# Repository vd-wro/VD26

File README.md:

# WRO VizDrive 2026

Welcome to the project repository for the **Panamanian 🔴⚪🔵 Team VizDrive** for the **World Robot Olympiad (WRO)** 2026!
Here you will find all the documentation, source code, images, and models related to our autonomous robot.

## About VizDrive's Legacy

VizDrive started in 2025, and now keeps thriving with the same young Panamanians that started the project. For this updated 2026 repository, we have kept ViZio's previous versions for better understanding and comparison from our engineering process.

## Project Summary

VizDrive's core, ViZio, is an autonomous robot designed to navigate a closed-loop circuit, maintaining a stable trajectory with gyroscopic correction. It uses artificial vision, in conjunction with ultrasonic and color sensors, to detect walls and avoid obstacles.

We are participating in the **Future Engineers Category** to develop our skills and demonstrate the capabilities of young Panamanians in a competitive field like robotics.

During the creation of our robot, we tried to push the **fundamentals of robotics** to the highest we could. As you go through this GitHub repository, you may notice that we worked with very basic sensors (the kind typically found in standard Arduino kits), and that we strived to optimize them to the best of our capacities. This is because we aimed to make our build accessible for everyone, and show that even with the simplest components, it is possible to create truly functional robotic systems.

We would like to invite you into this short, 3 minute summary video to have a fresh start on our robot's construction, logic, and GitHub organization.

> [!NOTE]
> Throughout the competition, we are constantly making modifications in the software and hardware of our robot. We try to update on all the changes we make, but if you notice any inconsistency between the pages of the documentation, please let us know!

---

## General Project Index

You can use this index to navigate through our robot's documentation. Each document provides detailed information on every aspect of its operation:

* [**1. General Project Overview**](./docs/01_project_overview.md)
  * General and concise introduction to the robot and its main components.
  * Describes the robot's operational phases and workflow diagram.
* [**2. Hardware and Components of the Robot**](./docs/02_hardware_components.md)
  * Detailed specifications of all integrated electronic and mechanical hardware.
  * [General Electromechanical Diagram](./schemes/electromechanical_diagram.png)
  * [Circuit Interactive Design (Cirkit)](https://vd-wro.github.io/VD26/embeds/interactive_circuit)
  * [KiCad Files](./src/kicad_pcb)
* [**3. Software Architecture**](./docs/03_software_architecture.md)
  * Overview of software libraries, core functionalities, and code structure.
  * [Autonomous Driving Code](./src/main_control/Vizdrive_WRO_code.ino)
* [**4. Sensor and Pin Configurations**](./docs/04_sensors_and_pin_configuration.md)
  * In-depth review of each sensor, its role in the functionality, and Arduino pin assignments.
  * [Sensors' Test Codes](./src/test_code/)
* [**5. Robot Mobility Functionality**](./docs/05_robot_mobility.md)
  * Focuses on the robot's motion system, motor configuration, and steering mechanisms.
* [**6. PID Control for the Gyroscope**](./docs/06_pid_gyroscope_control.md)
  * Explains the MPU gyroscope implementation and PID control for trajectory stability.
  * [MPU Calibration Code](./src/mpu_orientation_control/mpu_calibration/mpu_calibration.ino)
  * [MPU Calibration Data Graph](./assets/data_graphs/MPU%20Calibration%20Data%20Analysis.xlsx)
* [**7. Computer Vision Functions**](./docs/07_computer_vision.md)
  * Covers the PixyCam's vision-based obstacle evasion.
  * [Computer Vision Code](./src/computer_vision/computer_vision.ino)
* [**8. Ultrasonic Distance Sensing and PID**](./docs/08_ultrasonic_distance_sensing.md)
  * Covers the distance measurement and wall avoidance with ultrasonic sensors, and the filters implemented to adjust precision.
  * Introduces and explains the side PID system for straight-line driving.
  * [Ultrasonic Sensor Data Analysis](./assets/data_graphs/Ultrasonic%20Sensors%20Data%20Analysis.xlsx)
* [**9. Color Detection Functions**](./docs/09_color_detection.md)
  * Explains the color sensor's applications and calibration.
* [**10. 3D Modeling and Fabrication**](./docs/10_3d_modeling.md)
  * Details the 3D design process, mechanical characteristics, and fabrication parameters.
  * [3D Models STL](./models/)
* [**11. Other Resources and User Manual**](./docs/11_other_resources.md)
  * User manual for robot's operation and calibration.
  * Summarized documentation and additional relevant resources and materials.
  * Highlighted technical issues and applied fixes.
* [**12. Building Instructions**](./docs/12_building_instruction.md)
  * Visual resources and explanations for ViZio's construction.
  * Construction animations and renders.

---

## ViZio Versions

| Versions                  | Problems | Improvements made          | Used In          | 
| :--------------------------- | :--------------------------- | :------------------------------------------- | :--------------------------------- | 
| Prototype               |     Often finding disconnected components.                    | N/a               | First prototype made. |
| ViZio                |     Gyroscope calibration, partial parking, connection problems due to cable wear, complications with the dual ultrasonic sensor. radar.                    | Removed clutter with a hand-soldered PCB.                 | 🇵🇦 Regionals 2025 |
| ViZio 2.0     |          Challenges with Pixy Parameters' calibration, incomplete parking maneuver, inverted SDA and SCL pins.          | Improved PCB, kept one frontal ultrasonic, new logic for parallel parking.      | 🇵🇦 National 2025 |
| ViZio V3                   |          Block color detection through Pixy, slower velocity.                | Fixed PCB, adaption to camera bug, new parallel parking logic that includes last block evasion.                 | 🇸🇬 WRO 2025 |
| ViZio IV    |      Poor power distribution caused servo peaks to drain the battery     | Changed camera, improved chassis, upgraded PCB, and added mechanical differential.      | 🇵🇦 Regionals & National 2026 |
| ViZio Phase V    |  N/a  | Coming soon...      | 🇵🇷 WRO 2026 |

For better comprehension please visit [**Previous Versions of our Robot**](./docs/11_other_resources.md#119-version-history)

---

## Photos and Videos

* **Team Photos:** [View Photos](./t-photos/README.md)
* **Vehicle Photos:** [View Photos](./v-photos/README.md)
* **Demonstration Videos:** [View Videos](./video/README.md)

---

## Source Code

All control and test codes are located in the `src/` folder.

* [Autonomous Driving (Obstacle Avoidance)](./src/main_control/Vizdrive_WRO_code.ino)
* [Autonomous Driving (No Obstacle Avoidance)](./src/main_control/Open_Round.ino)
* [MPU Orientation Control (PID and Calibration)](./src/mpu_orientation_control/pid_gyroscope.ino)
* [Computer Vision (PixyCam 2.1)](./src/computer_vision/computer_vision.ino)
* [Sensors' Test Codes](./src/test_code/)

---

## 3D Models

Files for 3D printed components are located in the `models/` folder in `.stl` files.
To access interactive models of each component, hosted in GitHub pages, visit `embeds/`.

* [Robot 3D Models](./models/)
* [Interactive 3D Models](./embeds/)

A version of our Unity Simulator, used during the robot's construction and planification process, is available as an HTTP embed, hosted with GitHub pages.

* [Unity Simulator Information](./embeds/Unity_simulator)
* [Unity Web Player](https://vd-wro.github.io/VD26/embeds/Unity_simulator/)

---

## Diagrams and Graphs

Flowcharts, circuits, and relevant data graphs.

* [Operation Flowcharts](./assets/flowcharts)
* [Calibration Data Graphs](./assets/data_graphs/)
* [Additional Hardware Photos](./assets/hardware_photos/)

---

## Team Members 🙋‍♂️🙋‍♀️🙋

|                                                       |                                                              |                                                        |
|:-----------------------------------------------------:|:-----------------------------------------------------------:|:-------------------------------------------------------:|
|        |  |              |
| [**ALEXIS PALACIOS NG**](./t-photos/meet_the_team/Alexis.md) <br> *Software Engineer*       | [**AISLINN CHAWLA ARORA**](./t-photos/meet_the_team/Aislinn.md) <br> *Logistics and Creativity*        |  [**CARLO HO NG**](./t-photos/meet_the_team/Carlo.md) <br> *Hardware Engineer*   |
Sensor Integration, <br>Firmware Architecture, <br>Code Logic, <br>Error Management, <br>Data Analysis, <br>GitHub Repository | Engineering Journal, <br>Drafting, <br>GitHub Repository, <br>Soldering, <br>Photography and Film, <br>Competition Planning|  Construction, <br>Wiring, <br>Circuit and PCB Design, <br>Power Management, <br>3D Modeling and Planning, <br>Animation, Illustration, Editing  |

---

## Special Thanks

We are profoundly thankful to everyone who has supported us on our journey so far! We're incredibly grateful to our school administration for providing the resources and trust needed to pursue this challenge. To our teachers, thank you for your guidance and advice during our preparation; we especially appreciate your patience with our absences for robot practices (we promise to catch up on our assignments after the Olympiad 😅). A special shout-out to our friends who spent their free time supporting us, cheering us on, and helping us stay up to date. To our amazing parents, your assurance and belief in us have been the foundation of our efforts, allowing us to participate even though it meant missing many classes. And last but certainly not least, to our incredible coach, Professor Agustín Rogelio Orro Pérez. Even while mentoring five other teams, you still found time to guide us through it all. Your expertise, leadership, and dedication have been invaluable for us.

Thank you all!

---

For any inquiry, question, or recommendation, feel free to contact us via email: **<vizdrive.wro@gmail.com>**

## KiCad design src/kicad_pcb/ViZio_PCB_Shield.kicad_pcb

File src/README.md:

# Souce Code Directory

Here you can find all the .ino files for the operation of our robot in the Open and Obstacle Challenges.
As well, you can find the test codes we used throughout the process of construction and debugging, besides the codes for data recolection and analysis for the ultrasonic sensors and the MPU6050.

The directory is organized in the following way:

## `src/07_computer_vision`

You will find the test code for the Pixycam 2.1 artificial vision and color signature detection. 

## `src/main_control`

You'll find the updated main code for the WRO competition challenges.

When you refer to the main source code, please consider that it is updated throughout the competition to improve or add different features, so it may vary between rounds.
In particular, the PID control constants, the amount of correction, and the different thresholds are modified depending on the performance.
You can see progress and changes over time by viewing previous versions in GitHub commits.

## `src/mpu_orientation_control`

You will find the test code and data recolection code for the MPU6050 gyroscope + accelerometer.

## `src/ultrasonic_sensors`

You will find the test code for raw measurements, the test code for filtered measurements, and the code for data recolection to compare how the error dispersion varies between raw and filtered measurements.

## `src/test_code`

You will find the general test codes for other functionalities as the color sensors suite, mainly to adjust the thresholds, or a code to test the motor and IR encoder.

## `src/kicad_pcb`

You will find the circuit files for our custom PCB.

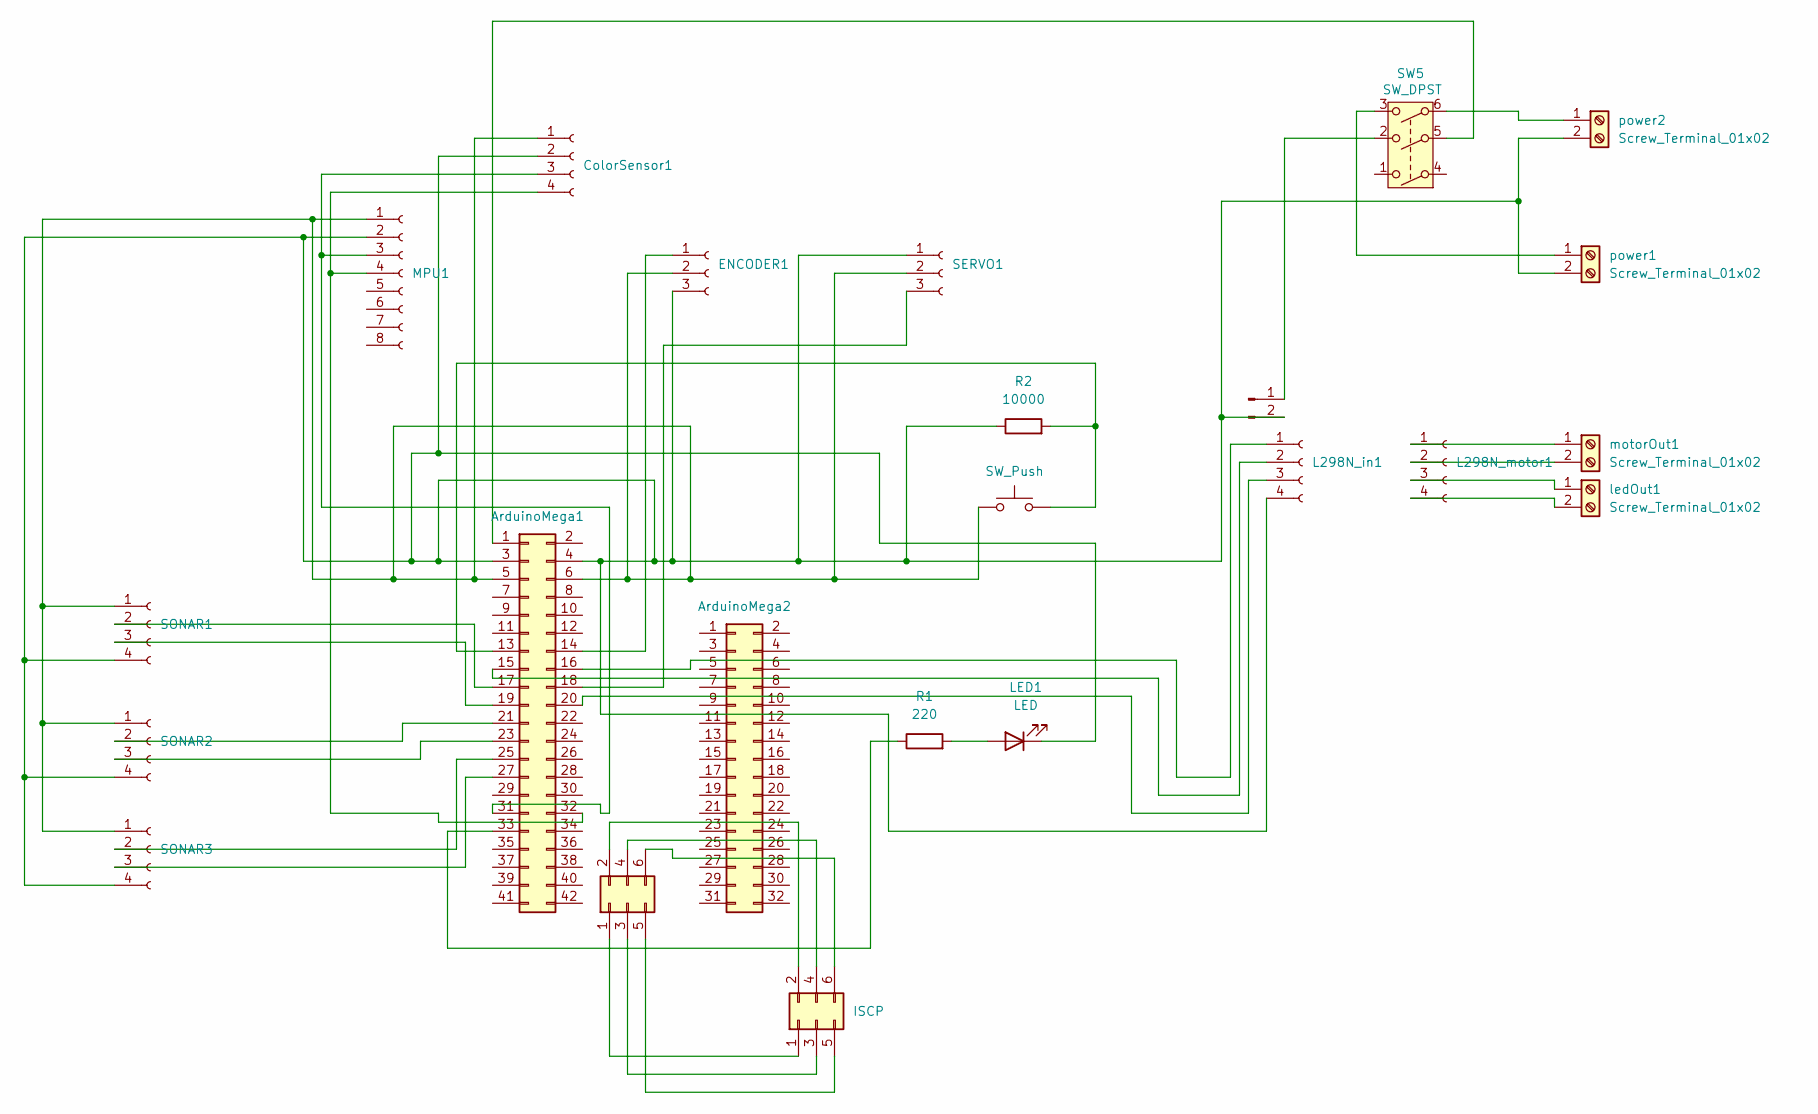
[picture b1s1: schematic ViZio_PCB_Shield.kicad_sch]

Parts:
ColorSensor1: Conn_01x04_Socket; PinSocket_1x04_P2.54mm_Vertical
ENCODER1: Conn_01x03_Socket; PinSocket_1x03_P2.54mm_Vertical
J1: ArduinoMega1; PinSocket_2x21_P2.54mm_Vertical
J2: ISCP; PinHeader_2x03_P2.54mm_Vertical
J3: ArduinoMega2; PinSocket_2x16_P2.54mm_Vertical
J4: Conn_02x03_Odd_Even; PinSocket_2x03_P2.54mm_Vertical
L298N_in1, L298N_motor1: Conn_01x04_Socket; PinSocket_1x04_P2.54mm_Vertical
L298N_power1: Conn_01x02_Pin; PinSocket_1x02_P2.54mm_Vertical
LED1: LED; LED_D5.0mm
MPU1: Conn_01x08_Socket; PinSocket_1x08_P2.54mm_Vertical
R1: 220; R_Axial_DIN0207_L6.3mm_D2.5mm_P10.16mm_Horizontal
R2: 10000; R_Axial_DIN0207_L6.3mm_D2.5mm_P10.16mm_Horizontal
SERVO1: Conn_01x03_Socket; PinHeader_1x03_P2.54mm_Vertical
SONAR1, SONAR2, SONAR3: Conn_01x04_Socket; PinSocket_1x04_P2.54mm_Vertical
SW1: SW_Push; SW_PUSH_6mm_H5mm
SW5: SW_DPST; SW_Push_2P2T_Toggle_CK_PVA2OAH5xxxxxxV2
ledOut1: Screw_Terminal_01x02; TerminalBlock_bornier-2_P5.08mm
motorOut1: Screw_Terminal_01x02; TerminalBlock_bornier-2_P5.08mm
power1, power2: Screw_Terminal_01x02; TerminalBlock_bornier-2_P5.08mm

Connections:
unnamed: ColorSensor1.2 (GND), ENCODER1.3 (GND), J1.3 (GND), J1.4 (GND), L298N_in1.4 (IN4), L298N_power1.2 (-), LED1.1 (K), MPU1.2 (GND), R2.1, SERVO1.1 (GND), SONAR1.4 (GND), SONAR2.4 (GND), SONAR3.4 (GND), power1.2 (-), power2.2 (-)
unnamed: ColorSensor1.3 (SCL), J1.31 (D21), MPU1.3 (SCL)
unnamed: ColorSensor1.4 (SDA), J1.32 (D20), MPU1.4 (SDA)
unnamed: ColorSensor1.1 (VCC), ENCODER1.2 (VCC), J1.5 (5V), J1.6 (5V), MPU1.1 (VCC), SERVO1.2 (VCC), SONAR1.1 (VCC), SONAR2.1 (VCC), SONAR3.1 (VCC), SW1.1
unnamed: ENCODER1.1 (OUT), J1.14 (D2)
unnamed: J1.13 (D3), R2.2, SW1.2
unnamed: J1.16 (D4), L298N_in1.1 (IN1)
unnamed: J1.15 (D5), L298N_in1.2 (IN2)
unnamed: J1.18 (D6), SERVO1.3
unnamed: J1.17 (D7), SONAR1.2 (TRIG)
unnamed: J1.20 (D8), L298N_in1.3 (IN3)
unnamed: J1.19 (D9), SONAR1.3 (ECHO)
unnamed: J1.21 (D11), SONAR2.2 (TRIG)
unnamed: J1.23 (D13), SONAR2.3 (ECHO)
unnamed: J1.25 (D15), SONAR3.2 (TRIG)
unnamed: J1.27 (D17), SONAR3.3 (ECHO)
unnamed: J1.33 (D23), R1.1
unnamed: J1.1 (VIN), SW5.5
unnamed: J2.1, J4.1
unnamed: J2.2, J4.2
unnamed: J2.3, J4.3
unnamed: J2.4, J4.4
unnamed: J2.5, J4.5
unnamed: J2.6, J4.6
unnamed: L298N_motor1.2 (MOTOR_A2), motorOut1.2 (-)
unnamed: L298N_motor1.1 (MOTOR_A), motorOut1.1 (+)
unnamed: L298N_motor1.4 (MOTOR_B2), ledOut1.2 (-)
unnamed: L298N_motor1.3 (MOTOR_B), ledOut1.1 (+)
unnamed: L298N_power1.1 (+), SW5.2
unnamed: LED1.2 (A), R1.2
unnamed: SW5.3, power1.1 (+)
unnamed: SW5.6, power2.1 (+)

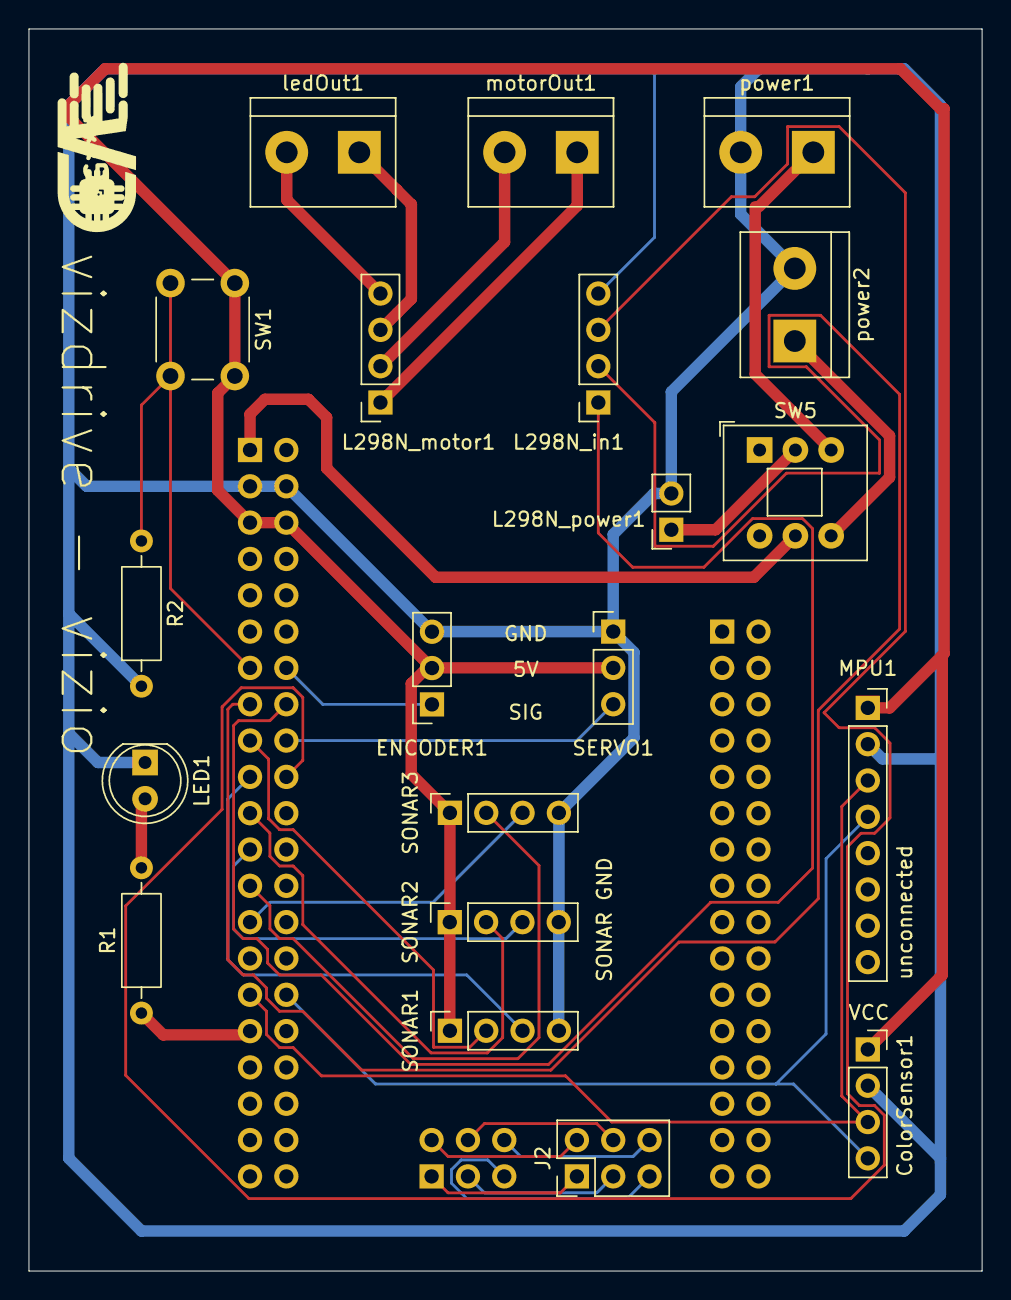
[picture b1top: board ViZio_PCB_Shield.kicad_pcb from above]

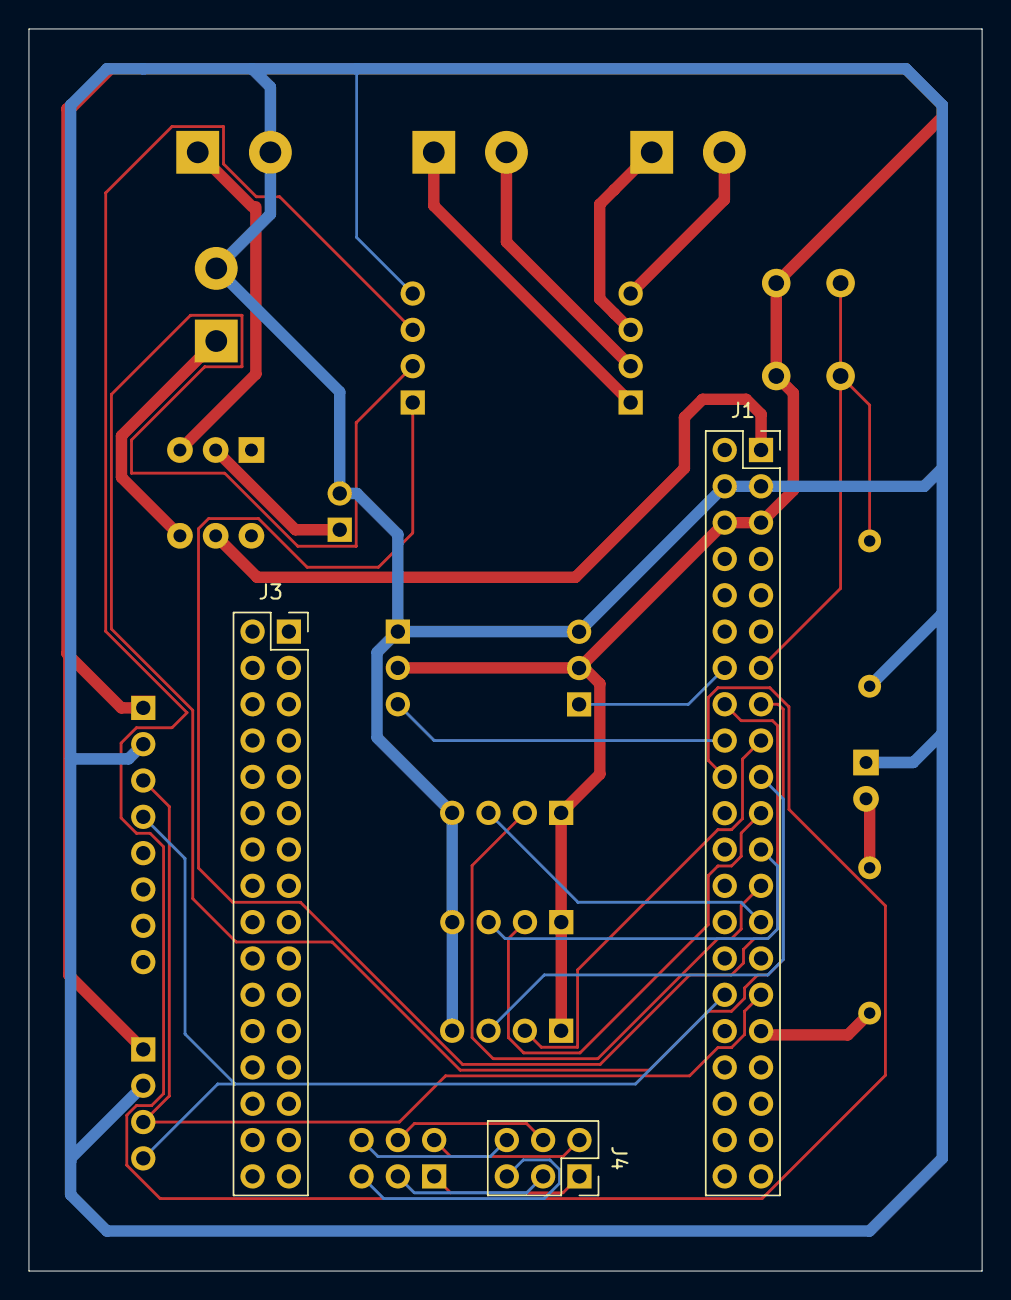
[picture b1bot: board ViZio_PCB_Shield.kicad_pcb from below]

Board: 2 copper layers, 66.7 x 86.9 mm, 23 parts (3 on the bottom side), 32 nets.

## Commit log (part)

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2025-07-08 Replaced the motor driver image
2025-07-08 Update 09_color_detection.md
    Added the precise color detection calculation
2025-07-08 Update 01_project_overview.md
    Clarification of the functionalities of the Open Challenge and the Obstacle Challenge.
2025-07-08 Update 03_software_architecture.md
    Explanations on the Open Round vs Challenge Round functionalities.
    Clarifications on the safeDelay() function.
2025-07-08 Update 04_sensors_and_pin_configuration.md
    Edited the ultrasonic configuration.
2025-07-08 Update 05_robot_mobility.md
    Added the exitParking() function
2025-07-08 Update 06_pid_gyroscope_control.md
    Modifications and clarifications on the calibration code.
2025-07-08 Update 07_pixycam_computer_vision.md
    Updated the new mechanism, PixyCam configuration and parameters and others.
2025-07-08 Update 08_ultrasonic_distance_sensing.md
    Updated the constrasting functions of the Open Challenge Round and the Obstacle Challenge Round.
2025-07-08 Update 09_color_detection.md
    Added the handleColorAction() function according to the Challenge.
2025-07-08 Update 06_pid_gyroscope_control.md
    Added hyperlink to 09_color_detection.md
2025-07-08 Update 11_other_resources.md
    Added the ultrasonic data graph. More to add into the miscelaneous section.
2025-07-09 Update README.md for embeds
2025-07-09 Update README.md for Unity Simulator
2025-07-09 Uploaded a web capture
2025-07-09 Update README.md
    For aesthetics
2025-07-09 Create README.md for hardware_photos
    Parcial creation of the hardware photos information.
2025-07-09 Update 09_color_detection.md
    Corrections.
2025-07-09 Uploaded the .gif of the logo
2025-07-09 Rename aislinn_1.jpg to aislinn_3.jpg
2025-07-09 Added the team member's photos
2025-07-09 Created README.md for the t-photos folder
2025-07-10 Update README.md for the video folder
2025-07-10 Upload the vehicle photos from all angles
2025-07-10 Create README.md for v-photos
2025-07-10 Update README.md
    Update links to photos and code
2025-07-10 Update README.md for videos
    Added the construction and music videos
2025-07-10 Uploaded the ultrasonic median filter code
2025-07-10 Update 11_other_resources.md
    Added the user manual.
2025-07-10 Update README.md for hardware photos
2025-07-10 Update README.md
    grammar
2025-07-10 Update Vizdrive_WRO_code.ino
    Updated the newest version of our code.
2025-07-12 Create Carlo.md for Meet The Team
2025-07-12 Create Aislinn.md for Meet The Team
2025-07-15 Update 02_hardware_components.md
    Updated the energy source
2025-07-15 Uploaded the 4.2V battery img
2025-07-29 Update 02_hardware_components.md
    Error 404
2025-07-29 Update README.md
    error 404
2025-09-30 Updating Github
2025-09-30 Added the kicad scheme
2025-10-01 Bug Fixes
2025-11-16 Added V3 Logo
2025-11-18 Updating src/kicad_pcb directory
2025-11-18 Create kicad_pcb
2025-11-18 Create file
2025-11-18 Revise hardware components documentation
2025-11-18 Document I2C bus fix and update images
2025-11-18 Update I2C bus images in hardware components documentation
2025-11-18 Fix image height in hardware components documentation
2025-11-19 Update 3D model links in documentation
    Added final and international 3D model links for the chassis.
2025-11-19 Fix grammar and clarity in ViZio 2.0 section
    Corrected grammatical errors and improved clarity in the description of ViZio 2.0.
2025-11-19 Fix typos in ViZio documentation
    Corrected typos and improved clarity in the documentation for the ViZio robot versions.
2025-11-19 Add link to International 3D Model for chassis
    Added link to the International 3D Model of the chassis.
2025-11-19 Fix link to 3D Modeling document
    Updated the reference link to the 3D Modeling document for better clarity.
2025-11-19 Update README with new chassis information
2025-11-19 Fix formatting in README.md for chassis section
2025-11-19 Update README with International Robot details
2025-11-19 Fix file name for International Chassis in README
    Corrected the file name for the International Chassis in the table.
2025-11-19 Update README with new chassis model information
2025-11-19 Correct formatting for Pivoting Maneuvers section
    Fixed formatting issue in the documentation regarding pivoting maneuvers.
2025-11-19 Change ViZio V3 image from PNG to JPG
    Updated image format for ViZio V3 hardware photo.
2025-11-19 Change ViZio 2.0 image in other resources
    Updated image reference for ViZio 2.0 in documentation.
2025-11-19 Document realignment method for robot positioning
    Added a realignment method for the robot to bump against the outer wall for better positioning.
2025-11-19 Fix formatting and punctuation in technical issues section
    Corrected formatting and punctuation in the technical issues section for clarity.
2025-11-19 Updated avoidWallPID function details
    Updated the section on the avoidWallPID function to clarify its purpose, operation, and the conditions under which it runs. Added detailed explanations for timing control, error calculation, and yaw 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
2025-11-19 Refine documentation for ultrasonic distance sensing
    Updated explanations for sonar sensor setup and PD control logic.
2025-11-19 Refactor avoidWallPID section for clarity
    Updated the formatting and structure of the section on the avoidWallPID function to improve clarity and readability.
2025-11-19 Fix formatting and update ultrasonic distance sensing doc
2025-11-19 Enhance documentation for avoidWallPID function
    Expanded the explanation of the avoidWallPID function, detailing its purpose, operation, timing control, setup, lateral PD control, yaw adjustment logic, and new target yaw application.
2025-11-19 Add avoidWallPID function code snippet
    Added code snippet for avoidWallPID function.
2025-11-19 Fix formatting of avoidWallPID code
    Updated code block formatting for avoidWallPID function.
2025-11-19 ViZio V3 New Images
2025-11-19 Updated robot pictures.
    Changed all the pictures to the new ViZio V3 International bot pictures.
2025-11-19 Enhance documentation with delay functions table
    Added a table summarizing delay functions and their purposes.
2025-11-19 Update section numbers in software architecture doc
2025-11-19 Update documentation for safeDelay functions
    Clarify the purpose and operation of safeDelay functions in the documentation.
2025-11-19 Fix duplicate line in software architecture documentation
2025-11-19 Replace safeDelay with safeDelayColor in evasion logic
    Updated delay functions to use safeDelayColor for better handling of yaw error during evasion.
2025-11-19 Update contact information section in documentation
    Removed and then re-added contact information for feedback and inquiries.
2025-11-19 Document performance improvement by soldering MPU
    Added a note on the performance improvement achieved by soldering the MPU to reduce vibrations.
2025-11-19 Update Pixy calibration instructions for clarity
    Clarified instructions for Pixy calibration regarding lens covering during initialization.
2025-11-19 Update team member skills in README
2025-11-19 Updated description of ViZio's name
2025-11-19 Revise video links and add new video explanation
    Updated video links and descriptions in README.
2025-11-19 Clarify robot animation video content in README
    Updated the README to clarify the purpose of the robot animation videos and added a link to the first video.
2025-11-20 Rename embeds/ViZio_PCB.glb to embeds/models_glb/ViZio_PCB.glb
2025-11-20 Create Interactive_KiCad_PCB
2025-11-20 Rename Interactive_KiCad_PCB to Interactive_KiCad_PCB.html
2025-11-21 Update 01_project_overview.md
    Updated the Flow Diagram
2025-11-21 Rename flowchart.png to previous_flowchart.png
2025-11-21 Upload the new workflow diagrams
2025-11-21 Create README.md for Workflow Diagrams
2026-06-16 Update project year from 2025 to 2026
2026-06-16 Correct year for World Robot Olympiad in overview
    Updated the year of the World Robot Olympiad from 2025 to 2026.
2026-06-16 Update year in project repository description
2026-06-21 ViZio IV update
2026-06-21 Force fix missing changes for VD26
2026-06-21 Add missing folder and files
2026-06-21 Restore V4 project state from VS Code Timeline recovery
2026-06-21 Update Carlo Photo
2026-06-21 Change link for previous robot versions
    Updated link for previous versions of the robot to point to a new documentation location.
2026-06-21 Rename Carlo_1.jpg to carlo_1.jpg
2026-06-21 Lower Resolution Carlo Photo
2026-06-21 Fix table formatting in hardware components documentation
2026-06-21 Update
    Fixing minor inconsistencies between sentences
2026-06-21 Refine AWB and auto-gain description in documentation
    Clarified the explanation of AWB and auto-gain settings for camera initialization.
2026-06-21 Refine AWB and auto-gain description in documentation
    Clarified the explanation of AWB and auto-gain settings for camera initialization, correcting terminology and improving readability.
2026-06-21 Increase steering angle from 50° to 55°
2026-06-21 Update ViZio IV chassis embed link
2026-06-21 Fix link for 2026 Chassis Models in README
    Updated link for 2026 Chassis Models to point to documentation.
2026-06-21 Update README with new video sections
    Added a new section for the differential assembly video
2026-06-21 Add additional ViZio IV video link
2026-06-22 Updated timeline - branding
2026-06-22 Timeline update
2026-06-22 Update ViZio IV video link in resources
2026-06-22 Replace differential assembly video thumbnail link
    Updated video links in README for differential assembly.
2026-06-22 Update project dimensions in overview document
2026-06-22 Update hardware components documentation
    Removed outdated components PixyCam 2.1 and TCS3200 Color Sensor from the hardware documentation. Added a new section for removed components.
2026-06-22 Update current draw information for OpenMV H7
2026-06-22 Revise hardware components section and update PCB details
    Removed sections on original and Arduino MKR1010 circuit designs, and added details about the new custom KiCad PCB circuit for the Mega 2560 Pro, including improvements and fixes.
2026-06-22 Correct capitalization of 'OpenMV H7 Plus'
2026-06-22 Correct OpenMV H7 Plus spelling in documentation
2026-06-22 Correct spelling of 'Artificial Vision' and 'OpenMV H7 Plus'
2026-06-22 Fix capitalization in OpenMV H7 Plus section
2026-06-22 Fix typo in robot mobility documentation
2026-06-22 Fix spelling errors in computer vision documentation
    Corrected spelling errors in the explanation of camera settings and white balance configuration.
2026-06-22 Fix typo in blob detection explanation
2026-06-22 Fix spelling errors in computer vision documentation
    Corrected spelling errors in the Size Filtering and Data Transmission section.
2026-06-22 Corrected sensor model from TCS34725 to TCS3472
2026-06-23 Remove sensor placement logic section
    Removed section on sensor placement logic, including ultrasonic sensors, PCB circuit, and camera pitch angle adjustments.
2026-06-23 Fix spelling and grammar in README version table
    Corrected spelling and grammar issues in the versions table.
2026-06-23 Remove component selection section from documentation
    Removed the component selection section detailing the controller, artificial vision, distance sensing, and color detection components. Simplified the explanation of sensor choices and alternatives.
2026-06-23 Remove branding and version history sections
    Removed sections on branding, version history, and detailed descriptions of previous robot iterations to streamline documentation.
